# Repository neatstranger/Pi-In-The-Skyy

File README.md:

# Pi In The Skyy 

A PoE powered camera based on the Raspberry Pi Compute Module 4.
<br>

----

## Specs Overview
- Dual 22 Pin 0.5mm Pitch Camera Inputs
- Passive PoE In (8-60V)
- HDMI / UART Connectors For Troubleshooting
- Micro SD Card Slot

## Enclosure
The main body of the enclosure is designed to be 3D printed out of ASA, but PLA/PETG would work just as well. Acrylic dome found on Amazon.

## Camera Mounting Hole Compatability
As far as I can tell, any of the first party v1, v2, and v3 cameras should work with the existing mounting plate. HQ/GS will need a new plate.

## Flexible Printed Circuit (FPC) Cable
You will need a 22 pin to 15 pin adapter cable. This is the same cable you would need to attach a first party camera to a RPi Zero, CM4IO board, or RPi5
[15 Way 1mm Spacing to 22 Way 0.5mm Spacing](https://www.pishop.us/product/camera-cable-for-raspberry-pi-5/)

## Power In
**Passive** POE IN 8-60V        Positive(3,6) (4,5)  Negative(7,8) (1,2) <br>
I have tons of passive PoE injectors from Ubiquiti equipment laying around, so I grabbed one like this:
[PoE+ Ubiquiti Injector](https://www.bhphotovideo.com/c/product/1737953-REG/ubiquiti_networks_u_poe_at_802_3at_supported_poe_injector.html/?ap=y&ap=y&smp=y&smp=y&lsft=BI%3A5451&gad_source=1&gclid=Cj0KCQjwwuG1BhCnARIsAFWBUC2Srk6iD-r-BquvTg5gMVnUvmvvXXQUebGMEcndWcXucgtnzZV4jrsaAs08EALw_wcB)

All of the pairs don't have to exactly match, this one is +(4,5) , -(7,8). As long as you don't cross the expected negative and positive it should work just fine. Most PoE injectors on Amazon or otherwise will list the pinout in the description. 

Make sure you purchase one that is passive though. 
Active PoE requires components on the baord to negotiate power delivery. Which this carrier board doesn't have. We are just pulling the voltage from the center tap of the magnetics.

## Complete Part List
- [Raspberry Pi CM4](https://rpilocator.com/?cat=CM4)
- [v1, v2, v3 Camera Module](https://www.pishop.us/product/raspberry-pi-camera-module-3-wide/)
- [15 to 22 Pin Camera Cable](https://www.pishop.us/product/camera-cable-for-raspberry-pi-5/)
- Carrier Board has no source, but production files are ready to order from jlcpcb.com (Cost is ~$250 / 5 Boards)
- 3D Printed Case
- [100mm Acrylic Dome](https://www.amazon.com/dp/B07L6GLTNP?psc=1&ref=product_details)
- Various Fasteners and Heat Set Inserts. M3 for Most of Assembly, M2 For Camera Module
- [Gland For Cable Passthrough](https://www.mcmaster.com/5302N121/)

## Systemd Service for Streaming `/etc/systemd/system/camera-stream.service`
```
[Unit]
Description=open-source-nvr
Wants=network-online.target
After=network-online.target

[Service]
User=<user>
Group=<user>
Type=simple
ExecStart=/bin/sh /var/camstart.sh

[Install]
WantedBy=multi-user.target
```
^^^ Make sure to replace <user> with your login account.

## `/var/camstart.sh`
```
#!/bin/sh
rpicam-vid -t 0 --width 1920 --height 1080 --inline --nopreview --rotation 180 -o - | cvlc stream:///dev/stdin --sout '#rtp{sdp=rtsp://:8554/stream1}' :demux=h264

```

## After Creating both Files
```
sudo chmod +x /var/camstart.sh # make the service executable
sudo systemctl daemon-reload #reload the system file
sudo systemctl start camera-stream #start the camera stream
sudo systemctl enable camera-stream
```

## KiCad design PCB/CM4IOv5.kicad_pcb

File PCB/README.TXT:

These files have been created in version 6 of KiCAD.

Some of the 3d models need to be downloaded form the following places and put into the CM4IO.3shapes directory some models are approximations.

https://datasheets.raspberrypi.org/cm4/CM4-step.zip
https://www.amphenol-icc.com/pci-express-1001878311200tlf.html
https://www.te.com/global-en/product-171826-4.html
https://www.molex.com/molex/products/part-detail/memory_card_socket/5033981892

The models provided in the 3dmodels directory are from various manufacturers including Diodes, Hirose, MTCONN,Toby, TRXCOM. Terms and conditions for the use of the models remain with the original manufacture.

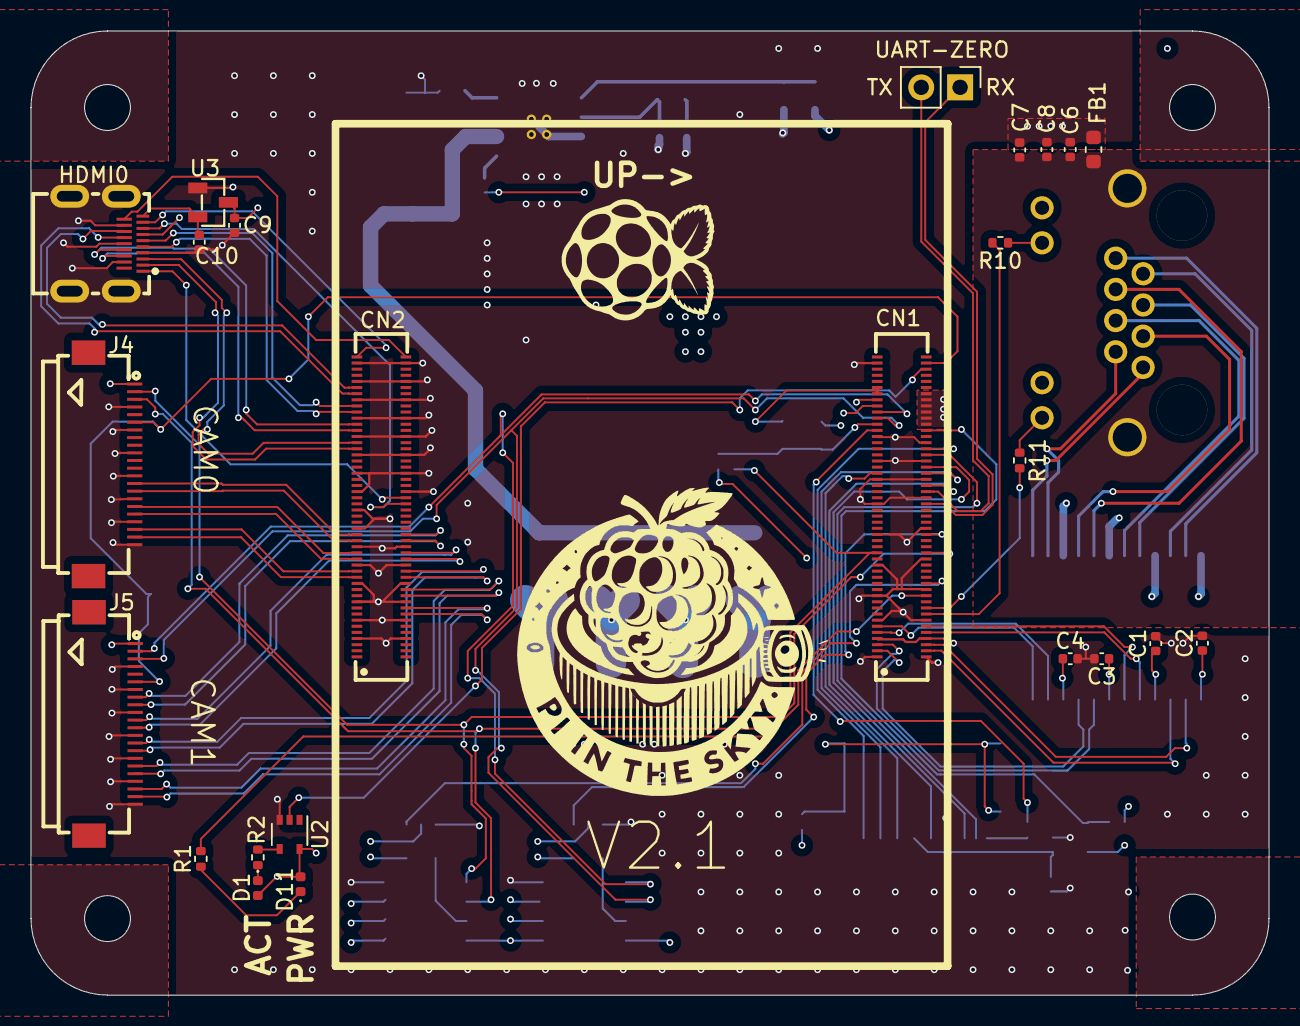
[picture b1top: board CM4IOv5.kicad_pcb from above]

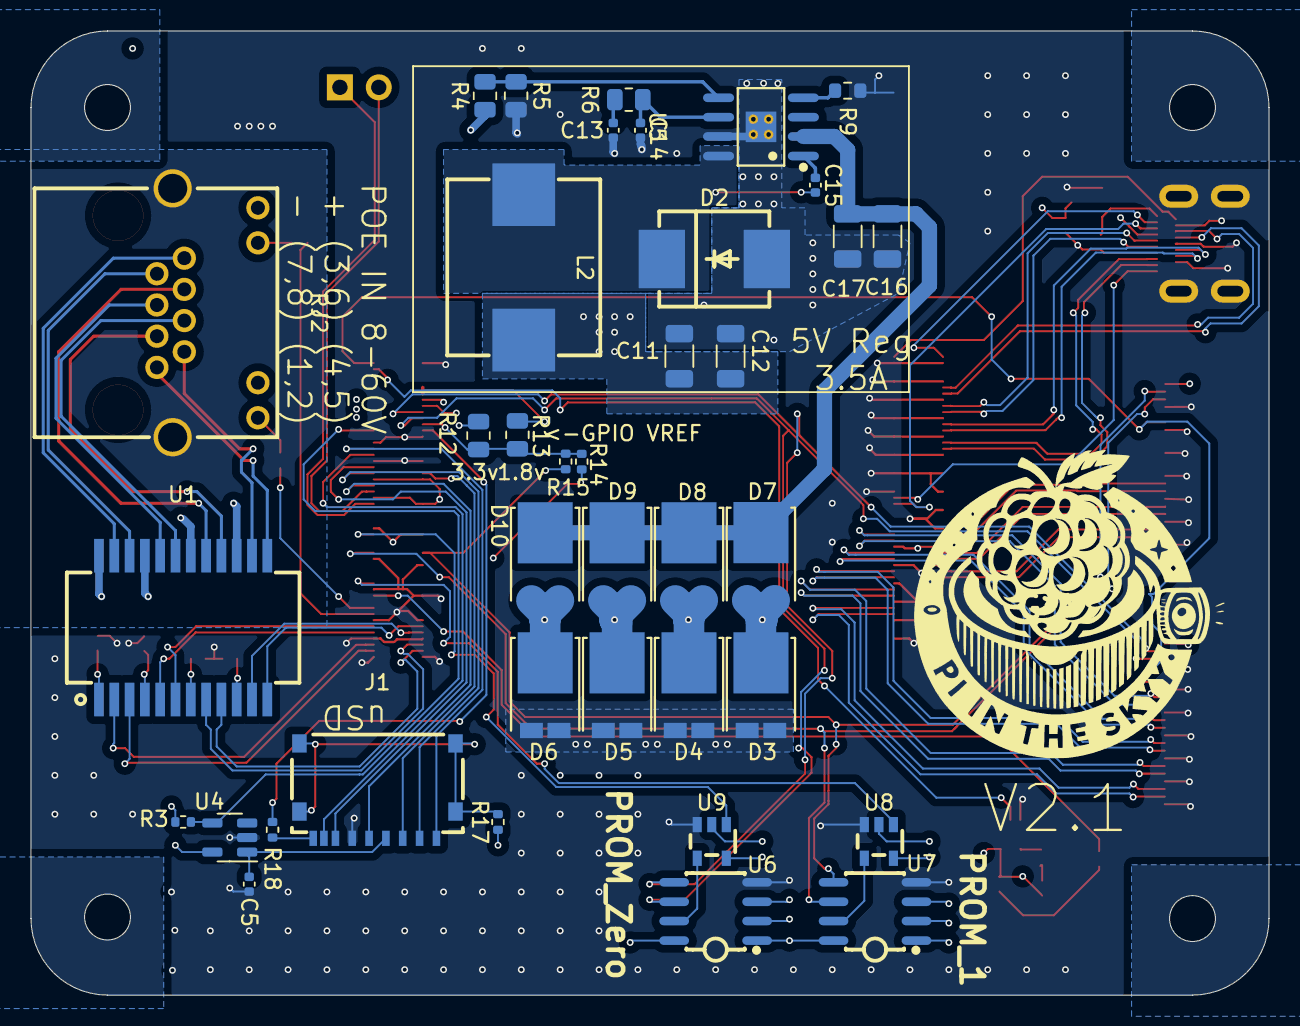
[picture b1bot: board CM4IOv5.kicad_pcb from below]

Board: 6 copper layers, 80.9 x 63.0 mm, 63 parts (38 on the bottom side), 97 nets.

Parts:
C1, C2, C3, C4, C6, C7, C8, C9, C10: 100n; C_0402_1005Metric
C5: 10u; C_0402_1005Metric
C11, C12: 47u; C_1206_3216Metric
C13: 6800p; C_0402_1005Metric
C14: 39p; C_0402_1005Metric
C15: 0.1u; C_0402_1005Metric
C16, C17: 2.2u; C_1206_3216Metric
CN1, CN2: DF40C-100DS-0.4V(51); CONN-SMD_DF40C-100DS-0.4V-51
D1: LED-RED; LED_0402_1005Metric
D2: B560C-13-F; SMC_L7.1-W6.2-LS8.1-RD
D3, D4, D5, D6, D7, D8, D9, D10: SB10100L; TO-277A_L4.7-W6.1-LS6.6-TR
D11: LED-Green; LED_0402_1005Metric
FB1: MPZ1608D101BTA00; L_0603_1608Metric
HDMI0: HDMI-101S; HDMI-SMD_HDMI-101S
J1: Micro_SD_Card_Det; TF-SMD_TF-018
J2: Conn_01x02_Pin; PinHeader_1x02_P2.54mm_Vertical
J4, J5: Conn_01x22_Female; FPC-SMD_22P-P0.50_FH12-22S-0.5SH-55
L2: FXL1040-8R2-M; IND-SMD_L11.5-W10.0_FXL1040
R1, R2: 1k; R_0402_1005Metric
R3: 12k; R_0402_1005Metric
R4: 53.6k; R_0805_2012Metric
R5: 10.2k; R_0805_2012Metric
R6: 13k; R_0805_2012Metric
R9: 162k; R_0603_1608Metric
R10, R11: 470; R_0402_1005Metric
R12: 0R; R_0805_2012Metric
R13: nf; R_0805_2012Metric
R14, R15: 2.2k; R_0402_1005Metric
R17, R18: nf; R_0402_1005Metric
RJ2: R-RJ45R08P-C000; RJ45-TH_R-RJ45R08P-C000
U1: QG2439S; SMD-24_L15.1-W7.1-P1.00-LS10.0-BL
U2: 74LVC1G07SE-7; SOT-353_SC-70-5
U3: AP2331SA-7; SOT-23-3_L2.9-W1.3-P1.90-LS2.4-BR
U4: RT9742GGJ5; SOT-23-5
U5: TPS54360BDDAR; SOIC-8_L5.0-W4.0-P1.27-LS6.0-BL-EP2.0
U6, U7: M24C64-WMN6TP; SOIC-8_L5.0-W4.0-P1.27-LS6.0-BL
U8, U9: 74LVC1G125GV-TP; SOT-23-5_L2.9-W1.6-P0.95-LS2.8-BR
UP->: LOGO

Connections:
/+3.3v: CN1.42, CN1.43, D1.2 (A), D11.2 (A), J4.1, J5.1, R3.1, R12.1, R17.1, RJ2.9 (L+), RJ2.11 (R+), U2.5 (VCC), U4.5 (IN), U6.1 (E0), U6.2 (E1), U6.3 (E2), U6.8 (VCC), U7.1 (E0), U7.2 (E1), U7.3 (E2), U7.8 (VCC), U8.2 (INA), U8.5 (VCC), U9.2 (INA), U9.5 (VCC)
/+5v: C9.1, C11.1, C12.1, CN1.57, CN1.58, CN1.59, CN1.60, CN1.61, CN1.62, L2.2, R4.1, U3.3 (IN)
/CM4_GPIO ( Ethernet, GPIO, SDCARD)/+1.8v: CN1.44, CN1.45, R13.1
/CM4_GPIO ( Ethernet, GPIO, SDCARD)/ActivityLED: CN1.90, R1.2
/CM4_GPIO ( Ethernet, GPIO, SDCARD)/BI_DA+: RJ2.1, U1.13
/CM4_GPIO ( Ethernet, GPIO, SDCARD)/BI_DA-: RJ2.2, U1.14
/CM4_GPIO ( Ethernet, GPIO, SDCARD)/BI_DB+: RJ2.3, U1.16
/CM4_GPIO ( Ethernet, GPIO, SDCARD)/BI_DB-: RJ2.6, U1.17
/CM4_GPIO ( Ethernet, GPIO, SDCARD)/BI_DC+: RJ2.4, U1.19
/CM4_GPIO ( Ethernet, GPIO, SDCARD)/BI_DC-: RJ2.5, U1.20
/CM4_GPIO ( Ethernet, GPIO, SDCARD)/BI_DD+: RJ2.7, U1.22
/CM4_GPIO ( Ethernet, GPIO, SDCARD)/BI_DD-: RJ2.8, U1.23
/CM4_GPIO ( Ethernet, GPIO, SDCARD)/ETH_LEDG: CN1.92, R11.2
/CM4_GPIO ( Ethernet, GPIO, SDCARD)/ETH_LEDY: CN1.93, R10.2
/CM4_GPIO ( Ethernet, GPIO, SDCARD)/GPIO14_UART0_TXD: CN1.73, J2.2
/CM4_GPIO ( Ethernet, GPIO, SDCARD)/GPIO15_UART0_RXD: CN1.75, J2.1
/CM4_GPIO ( Ethernet, GPIO, SDCARD)/GPIO21: CN1.88, U8.1 (~G)
/CM4_GPIO ( Ethernet, GPIO, SDCARD)/GPIO25: CN1.80, U9.1 (~G)
/CM4_GPIO ( Ethernet, GPIO, SDCARD)/GPIO_VREF: CN1.39, R12.2, R13.2, R14.2, R15.2
/CM4_GPIO ( Ethernet, GPIO, SDCARD)/ID_SC: CN1.83, J4.3, R14.1, U7.6 (SCL)
/CM4_GPIO ( Ethernet, GPIO, SDCARD)/ID_SD: CN1.18, J4.2, R15.1, U7.5 (SDA)
/CM4_GPIO ( Ethernet, GPIO, SDCARD)/POE_VDD+: C16.1, C17.1, D7.3, D8.3, D9.3, D10.3, U5.2 (VIN)
/CM4_GPIO ( Ethernet, GPIO, SDCARD)/PROM0_WC: U6.7 (~WC), U9.4 (OUTY)
/CM4_GPIO ( Ethernet, GPIO, SDCARD)/PROM1_WC: U7.7 (~WC), U8.4 (OUTY)
/CM4_GPIO ( Ethernet, GPIO, SDCARD)/PoE_IN_A+: D3.3, D7.1, D7.2, U1.21
/CM4_GPIO ( Ethernet, GPIO, SDCARD)/PoE_IN_A-: D4.3, D8.1, D8.2, U1.24
/CM4_GPIO ( Ethernet, GPIO, SDCARD)/PoE_IN_B+: D5.3, D9.1, D9.2, U1.18
/CM4_GPIO ( Ethernet, GPIO, SDCARD)/PoE_IN_B-: D6.3, D10.1, D10.2, U1.15
/CM4_GPIO ( Ethernet, GPIO, SDCARD)/Reserved: CN1.38, R18.1
/CM4_GPIO ( Ethernet, GPIO, SDCARD)/SD_CLK: CN1.72, J1.5 (CLK)
/CM4_GPIO ( Ethernet, GPIO, SDCARD)/SD_CMD: CN1.31, J1.3 (CMD)
/CM4_GPIO ( Ethernet, GPIO, SDCARD)/SD_DAT0: CN1.69, J1.7 (DAT0)
/CM4_GPIO ( Ethernet, GPIO, SDCARD)/SD_DAT1: CN1.67, J1.8 (DAT1)
/CM4_GPIO ( Ethernet, GPIO, SDCARD)/SD_DAT2: CN1.66, J1.1 (DAT2)
/CM4_GPIO ( Ethernet, GPIO, SDCARD)/SD_DAT3: CN1.70, J1.2 (DAT3/CD)
/CM4_GPIO ( Ethernet, GPIO, SDCARD)/SD_PWR: C5.1, J1.4 (VDD), U4.1 (OUT)
/CM4_GPIO ( Ethernet, GPIO, SDCARD)/SD_PWR_ON: CN1.63, R3.2, U4.4 (EN)
/CM4_GPIO ( Ethernet, GPIO, SDCARD)/TRD0_N: CN1.5, U1.11
/CM4_GPIO ( Ethernet, GPIO, SDCARD)/TRD0_P: CN1.6, U1.12
/CM4_GPIO ( Ethernet, GPIO, SDCARD)/TRD1_N: CN1.3, U1.8
/CM4_GPIO ( Ethernet, GPIO, SDCARD)/TRD1_P: CN1.2, U1.9
/CM4_GPIO ( Ethernet, GPIO, SDCARD)/TRD2_N: CN1.96, U1.5
/CM4_GPIO ( Ethernet, GPIO, SDCARD)/TRD2_P: CN1.95, U1.6
/CM4_GPIO ( Ethernet, GPIO, SDCARD)/TRD3_N: CN1.98, U1.2
/CM4_GPIO ( Ethernet, GPIO, SDCARD)/TRD3_P: CN1.99, U1.3
/CM4_GPIO ( Ethernet, GPIO, SDCARD)/nPWR_LED: CN1.53, U2.2
/CM4_HighSpeed/CAM0_C_N: CN2.20, J4.15
/CM4_HighSpeed/CAM0_C_P: CN2.21, J4.14
/CM4_HighSpeed/CAM0_D0_N: CN2.14, J4.21
/CM4_HighSpeed/CAM0_D0_P: CN2.15, J4.20
/CM4_HighSpeed/CAM0_D1_N: CN2.17, J4.18
/CM4_HighSpeed/CAM0_D1_P: CN2.18, J4.17
/CM4_HighSpeed/CAM1_C_N: CN2.87, J5.15
/CM4_HighSpeed/CAM1_C_P: CN2.86, J5.14
/CM4_HighSpeed/CAM1_D0_N: CN2.93, J5.21
/CM4_HighSpeed/CAM1_D0_P: CN2.92, J5.20
/CM4_HighSpeed/CAM1_D1_N: CN2.90, J5.18
/CM4_HighSpeed/CAM1_D1_P: CN2.89, J5.17
/CM4_HighSpeed/CAM1_D2_N: CN2.84, J5.12
/CM4_HighSpeed/CAM1_D2_P: CN2.83, J5.11
/CM4_HighSpeed/CAM1_D3_N: CN2.81, J5.9
/CM4_HighSpeed/CAM1_D3_P: CN2.80, J5.8
/CM4_HighSpeed/CAM_GPIO: CN1.52, J4.6, J5.6
/CM4_HighSpeed/HDMI0_CEC: CN2.75, HDMI0.15 (CEC)
/CM4_HighSpeed/HDMI0_CK_N: CN2.45, HDMI0.14 (TMDS_CLOCK-)
/CM4_HighSpeed/HDMI0_CK_P: CN2.44, HDMI0.12 (TMDS_CLOCK+)
/CM4_HighSpeed/HDMI0_D0_N: CN2.42, HDMI0.11 (TMDS_DATA0-)
/CM4_HighSpeed/HDMI0_D0_P: CN2.41, HDMI0.9 (TMDS_DATA0+)
/CM4_HighSpeed/HDMI0_D1_N: CN2.39, HDMI0.8 (TMDS_DATA1-)
/CM4_HighSpeed/HDMI0_D1_P: CN2.38, HDMI0.6 (TMDS_DATA1+)
/CM4_HighSpeed/HDMI0_D2_N: CN2.36, HDMI0.5 (TMDS_DATA2-)
/CM4_HighSpeed/HDMI0_D2_P: CN2.35, HDMI0.3 (TMDS_DATA2+)
/CM4_HighSpeed/HDMI0_HOTPLUG: CN2.74, HDMI0.1 (HOT_PLUG_DET)
/CM4_HighSpeed/HDMI0_SCL: CN2.50, HDMI0.17 (SCL)
/CM4_HighSpeed/HDMI0_SDA: CN2.51, HDMI0.18 (SDA)
/CM4_HighSpeed/HDMI_5v: C10.1, HDMI0.19 (+5V), U3.2 (OUT)
/CM4_HighSpeed/SCL0: CN1.40, J5.3, U6.6 (SCL)
/CM4_HighSpeed/SDA0: CN1.41, J5.2, U6.5 (SDA)
/PSUS/FB: R4.2, R5.1, U5.5 (FB)
ENET_GND: C6.2, C7.2, C8.2, FB1.1, RJ2.13 (S), RJ2.14 (S)
GND: C1.2, C2.2, C3.2, C4.2, C5.2, C6.1, C7.1, C8.1, C9.2, C10.2, C11.2, C12.2, C13.2, C14.2, C16.2, C17.2, CN1.1, CN1.4, CN1.7, CN1.11, CN1.16, CN1.21, CN1.26, CN1.30, CN1.33, CN1.37, CN1.49, CN1.65, CN1.68, CN1.71, CN1.74, CN1.79, CN1.84, CN1.89, CN1.94, CN1.97, CN1.100, CN2.4, CN2.7, CN2.10, CN2.13, CN2.16, CN2.19, CN2.22, CN2.25, CN2.28, CN2.31, CN2.34, CN2.37, CN2.40, CN2.43, CN2.46, CN2.49, CN2.52, CN2.55, CN2.58, CN2.61, CN2.64, CN2.67, CN2.70, CN2.73, CN2.82, CN2.85, CN2.88, CN2.91, CN2.94, CN2.97, D2.2 (A), D3.1, D3.2, D4.1, D4.2, D5.1, D5.2, D6.1, D6.2, FB1.2, HDMI0.4 (TMDS_DATA2_SHIELD), HDMI0.7 (TMDS_DATA1_SHIELD), HDMI0.10 (TMDS_DATA0_SHIELD), HDMI0.13 (TMDS_CLOCK_SHIELD), HDMI0.16 (DDC/CEC_GND), HDMI0.20 (SHIELD), J1.6 (VSS), J4.4, J4.7, J4.10, J4.13, J4.16, J4.19, J4.22, J5.4, J5.7, J5.10, J5.13, J5.16, J5.19, J5.22, R5.2, R9.2, U2.3 (GND), U3.1 (GND), U4.2 (GND), U5.7 (GND), U5.9 (PAD), U6.4 (VSS), U7.4 (VSS), U8.3 (GND), U9.3 (GND)
unnamed: C1.1, U1.4
unnamed: C2.1, U1.1
unnamed: C3.1, U1.7
unnamed: C4.1, U1.10
unnamed: C13.1, R6.2
unnamed: D1.1 (K), R2.1
unnamed: C15.2, D2.1 (K), L2.1, U5.8 (SW)
unnamed: D11.1 (K), R1.1
unnamed: J1.10 (DET_A), R17.2
unnamed: J1.9 (DET_B), R18.2
unnamed: R2.2, U2.4
unnamed: R10.1, RJ2.10 (L-)
unnamed: R11.1, RJ2.12 (R-)
unnamed: C15.1, U5.1 (BOOT)
unnamed: C14.1, R6.1, U5.6 (COMP)
unnamed: R9.1, U5.4 (RT/CLK)

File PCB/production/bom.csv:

Designator,Footprint,Quantity,Value,LCSC Part #
"C1, C10, C2, C3, C4, C6, C7, C8, C9",0402,9,100n,C309458
"C11, C12",1206,2,47u,C94034
C13,0402,1,6800p,C2760541
C14,0402,1,39p,C5186878
C15,0402,1,0.1u,C56392
"C16, C17",1206,2,2.2u,C170101
C5,0402,1,10u,C315248
"CN1, CN2",CONN-SMD_DF40C-100DS-0.4V-51,2,DF40C-100DS-0.4V(51),C597931
D1,0402,1,LED-RED,C434445
"D10, D3, D4, D5, D6, D7, D8, D9",TO-277A_L4.7-W6.1-LS6.6-TR,8,SB10100L,C113946
D11,0402,1,LED-Green,C434446
D2,SMC_L7.1-W6.2-LS8.1-RD,1,B560C-13-F,C85100
FB1,0603,1,MPZ1608D101BTA00,C87554
HDMI0,HDMI-SMD_HDMI-101S,1,HDMI-101S,C720620
J1,TF-SMD_TF-018,1,Micro_SD_Card_Det,C961679
"J4, J5",FPC-SMD_22P-P0.50_FH12-22S-0.5SH-55,2,Conn_01x22_Female,C597981
L2,IND-SMD_L11.5-W10.0_FXL1040,1,FXL1040-8R2-M,C167232
"R1, R2",0402,2,1k,C11702
"R10, R11",0402,2,470,C25167
R12,0805,1,0R,C17477
"R14, R15",0402,2,2.2k,C25879
R3,0402,1,12k,C102781
R4,0805,1,53.6k,C21398
R5,0805,1,10.2k,C217771
R6,0805,1,13k,C445658
R9,0603,1,162k,C22815
RJ2,RJ45-TH_R-RJ45R08P-C000,1,R-RJ45R08P-C000,C386757
U1,SMD-24_L15.1-W7.1-P1.00-LS10.0-BL,1,QG2439S,C3003223
U2,SOT-353_SC-70-5,1,74LVC1G07SE-7,C7464692
U3,SOT-23-3_L2.9-W1.3-P1.90-LS2.4-BR,1,AP2331SA-7,C500764
U4,SOT-23-5,1,RT9742GGJ5,C250547
U5,SOIC-8_L5.0-W4.0-P1.27-LS6.0-BL-EP2.0,1,TPS54360BDDAR,C524806
"U6, U7",SOIC-8_L5.0-W4.0-P1.27-LS6.0-BL,2,M24C64-WMN6TP,C7999
"U8, U9",SOT-23-5_L2.9-W1.6-P0.95-LS2.8-BR,2,74LVC1G125GV-TP,C3040595

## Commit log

2024-08-11 Updated .gitignore
2024-08-11 First push
2024-08-11 Trimmed Images
2024-08-11 Added Smaller Images
2024-08-11 Downsized images again.
2024-08-11 Create LICENSE
2024-08-11 Update LICENSE
    Added hardware inclusion since there is almost no software in this repo.
2024-08-14 Added Primary and Secondary EEPROM
    This will be used to store configuration separate from the OS.
2024-08-14 Had to go with an inverting buffer, to correctly setup the EEPROM
    The WC pin of the eeprom, disables writing when it is high. Default state has GPIO 25, and GPIO21 are pulled low.
    I want the EEPROM to disable writing until I am ready to write to it.
    During normal Pi Operation (GPIOlow) the eeprom is in the following state:
    Input A(+3.3V) = HIGH
    INPUT /G (GPIO) = LOW
    Output Y = LOW
2024-08-14 Routed EEPROM modules to SDA/SCL and GPIO pins.
    These are definitely taking up more space than they need to, but a little extra space will provide easier in-situ changes if rewiring is needed.
2024-08-14 Remove autosaves and locks.
2024-08-14 Added .gitignore to subdirectory.
2024-08-14 Updated fonts for export.
2024-08-14 Updated silkscreen for release.
    Exported STEP/JLC Production Files.
2024-08-14 Updated 3D images.
2024-08-21 Fixed hole connected to every plain.
2024-08-21 Moved silk screen to not clip.
